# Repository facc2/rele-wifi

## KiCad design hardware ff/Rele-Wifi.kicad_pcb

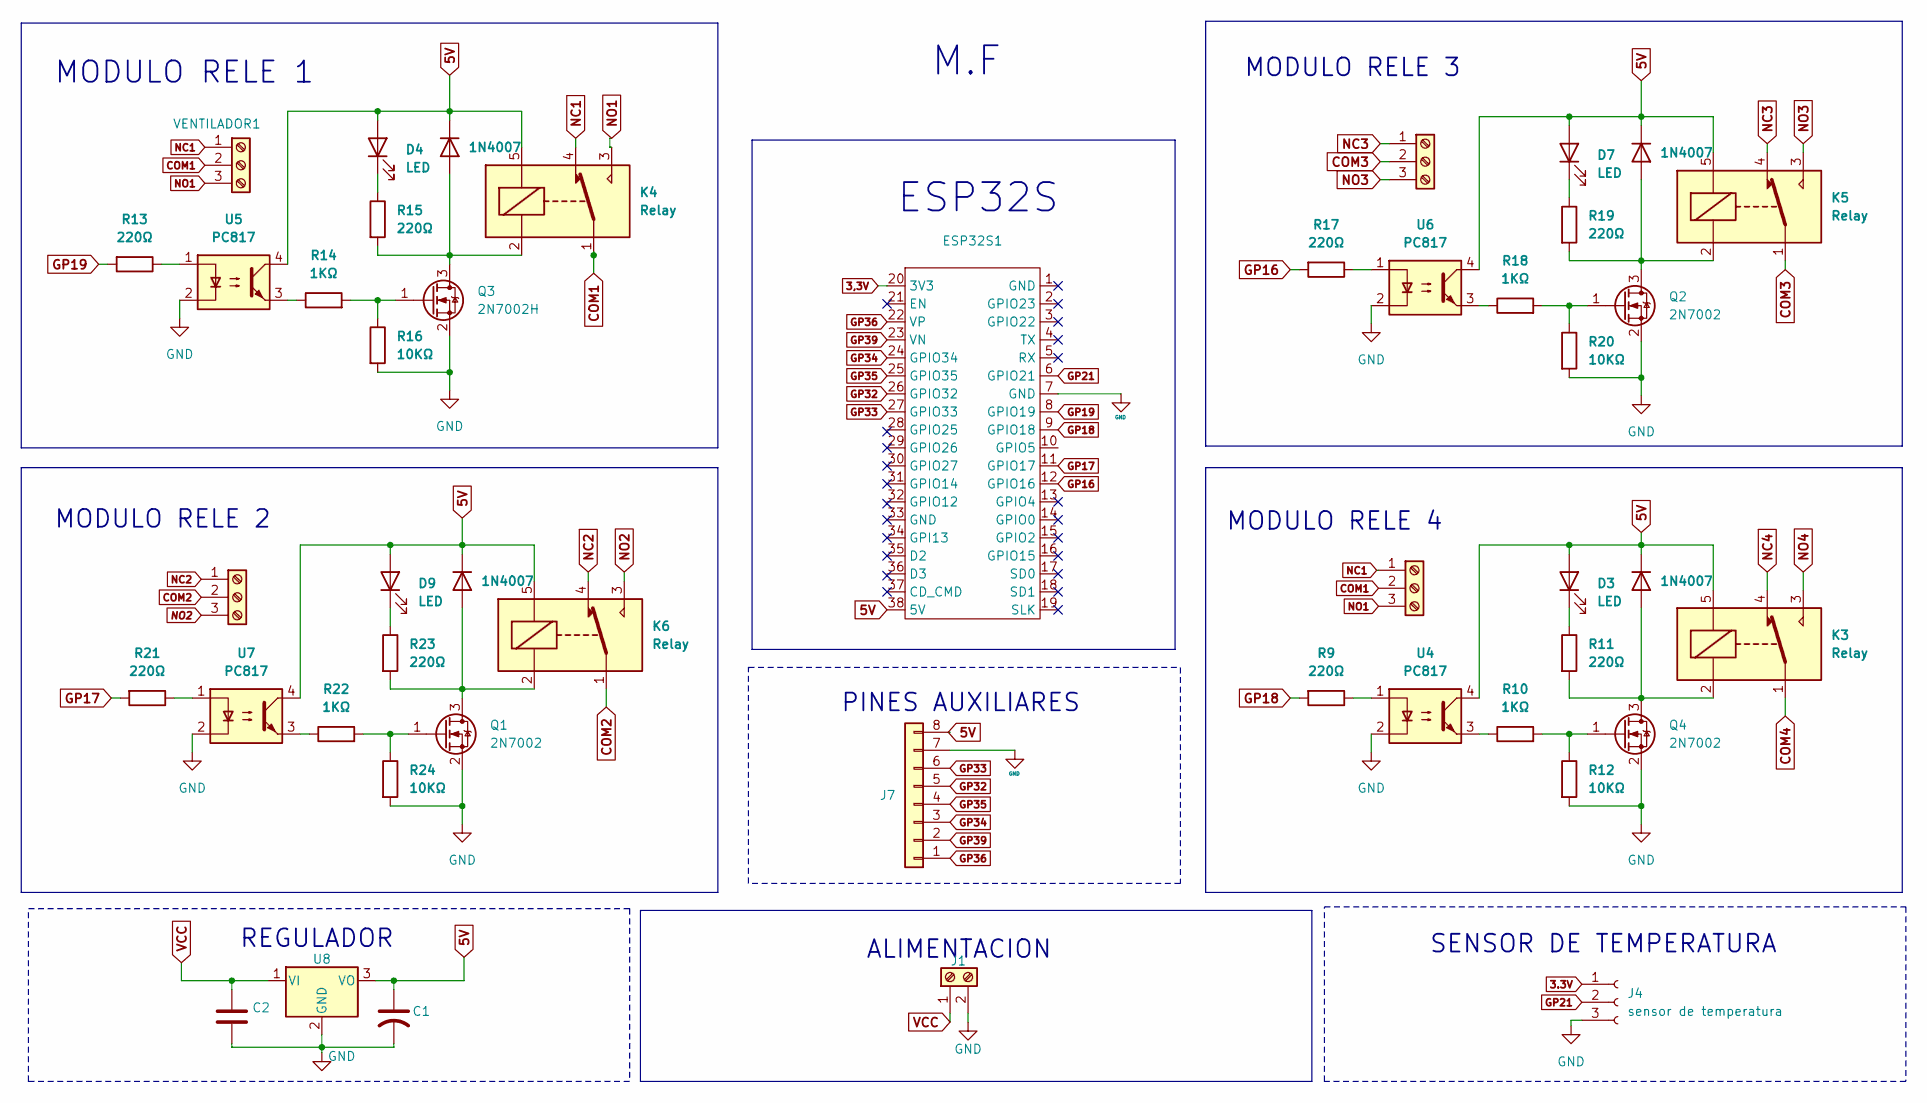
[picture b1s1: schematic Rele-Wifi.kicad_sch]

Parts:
C1: C_US; C_0805_2012Metric
C2: C; C_0805_2012Metric
D3, D4, D7, D9: LED; LED_0805_2012Metric
D5, D6, D8, D10: 1N4007; D_SMA
ESP32S1: ESP32S_38_PINES
J1: Screw_Terminal_01x02; TerminalBlock_MaiXu_MX126-5.0-02P_1x02_P5.00mm
J3, J5, J6: Screw_Terminal_01x03; TerminalBlock_MaiXu_MX126-5.0-03P_1x03_P5.00mm
J4: sensor de temperatura; PinSocket_1x03_P2.54mm_Vertical
J7: Conn_01x08; PinSocket_1x08_P2.54mm_Vertical
K3, K4, K5, K6: Relay; Relay_SPDT_SANYOU_SRD_Series_Form_C
Q1, Q2, Q4: 2N7002; SOT-23
Q3: 2N7002H; SOT-23
R9, R11, R13, R15, R17, R19, R21, R23: 220Ω; R_0805_2012Metric
R10, R14, R18, R22: 1KΩ; R_0805_2012Metric
R12, R16, R20, R24: 10KΩ; R_0805_2012Metric
U4, U5, U6, U7: PC817; DIP-4_W7.62mm
U8: KA78M05_TO252; TO-263-3_TabPin2
VENTILADOR1: Screw_Terminal_01x03; TerminalBlock_MaiXu_MX126-5.0-03P_1x03_P5.00mm

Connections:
3,3V: ESP32S1.20 (3V3)
3.3V: J4.1
5V: C1.1, D3.2 (A), D4.2 (A), D5.1 (K), D6.1 (K), D7.2 (A), D8.1 (K), D9.2 (A), D10.1 (K), ESP32S1.38 (5V), J7.8, K3.5, K4.5, K5.5, K6.5, U4.4, U5.4, U6.4, U7.4, U8.3 (VO)
COM1: J3.2, K4.1, VENTILADOR1.2
COM2: J6.2, K6.1
COM3: J5.2, K5.1
COM4: K3.1
GND: C1.2, C2.2, ESP32S1.7 (GND), J1.2, J4.3, J7.7, Q1.2 (S), Q2.2 (S), Q3.2 (S), Q4.2 (S), R12.2, R16.2, R20.2, R24.2, U4.2, U5.2, U6.2, U7.2, U8.2 (GND)
GP16: ESP32S1.12 (GPIO16), R17.2
GP17: ESP32S1.11 (GPIO17), R21.2
GP18: ESP32S1.9 (GPIO18), R9.2
GP19: ESP32S1.8 (GPIO19), R13.2
GP21: ESP32S1.6 (GPIO21), J4.2
GP32: ESP32S1.26 (GPIO32), J7.5
GP33: ESP32S1.27 (GPIO33), J7.6
GP34: ESP32S1.24 (GPIO34), J7.3
GP35: ESP32S1.25 (GPIO35), J7.4
GP36: ESP32S1.22 (VP), J7.1
GP39: ESP32S1.23 (VN), J7.2
NC1: J3.1, K4.4, VENTILADOR1.1
NC2: J6.1, K6.4
NC3: J5.1, K5.4
NC4: K3.4
NO1: J3.3, K4.3, VENTILADOR1.3
NO2: J6.3, K6.3
NO3: J5.3, K5.3
NO4: K3.3
unnamed: D3.1 (K), R11.1
unnamed: D4.1 (K), R15.1
unnamed: D5.2 (A), K3.2, Q4.3 (D), R11.2
unnamed: D6.2 (A), K4.2, Q3.3 (D), R15.2
unnamed: D7.1 (K), R19.1
unnamed: D8.2 (A), K5.2, Q2.3 (D), R19.2
unnamed: D9.1 (K), R23.1
unnamed: D10.2 (A), K6.2, Q1.3 (D), R23.2
unnamed: Q1.1 (G), R22.2, R24.1
unnamed: Q2.1 (G), R18.2, R20.1
unnamed: Q3.1 (G), R14.2, R16.1
unnamed: Q4.1 (G), R10.2, R12.1
unnamed: R9.1, U4.1
unnamed: R10.1, U4.3
unnamed: R13.1, U5.1
unnamed: R14.1, U5.3
unnamed: R17.1, U6.1
unnamed: R18.1, U6.3
unnamed: R21.1, U7.1
unnamed: R22.1, U7.3
VCC: C2.1, J1.1, U8.1 (VI)

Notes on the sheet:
MODULO RELE 3
MODULO RELE 4
ESP32S
MODULO RELE 1
M.F
ALIMENTACION
SENSOR DE TEMPERATURA
REGULADOR
PINES AUXILIARES
MODULO RELE 2

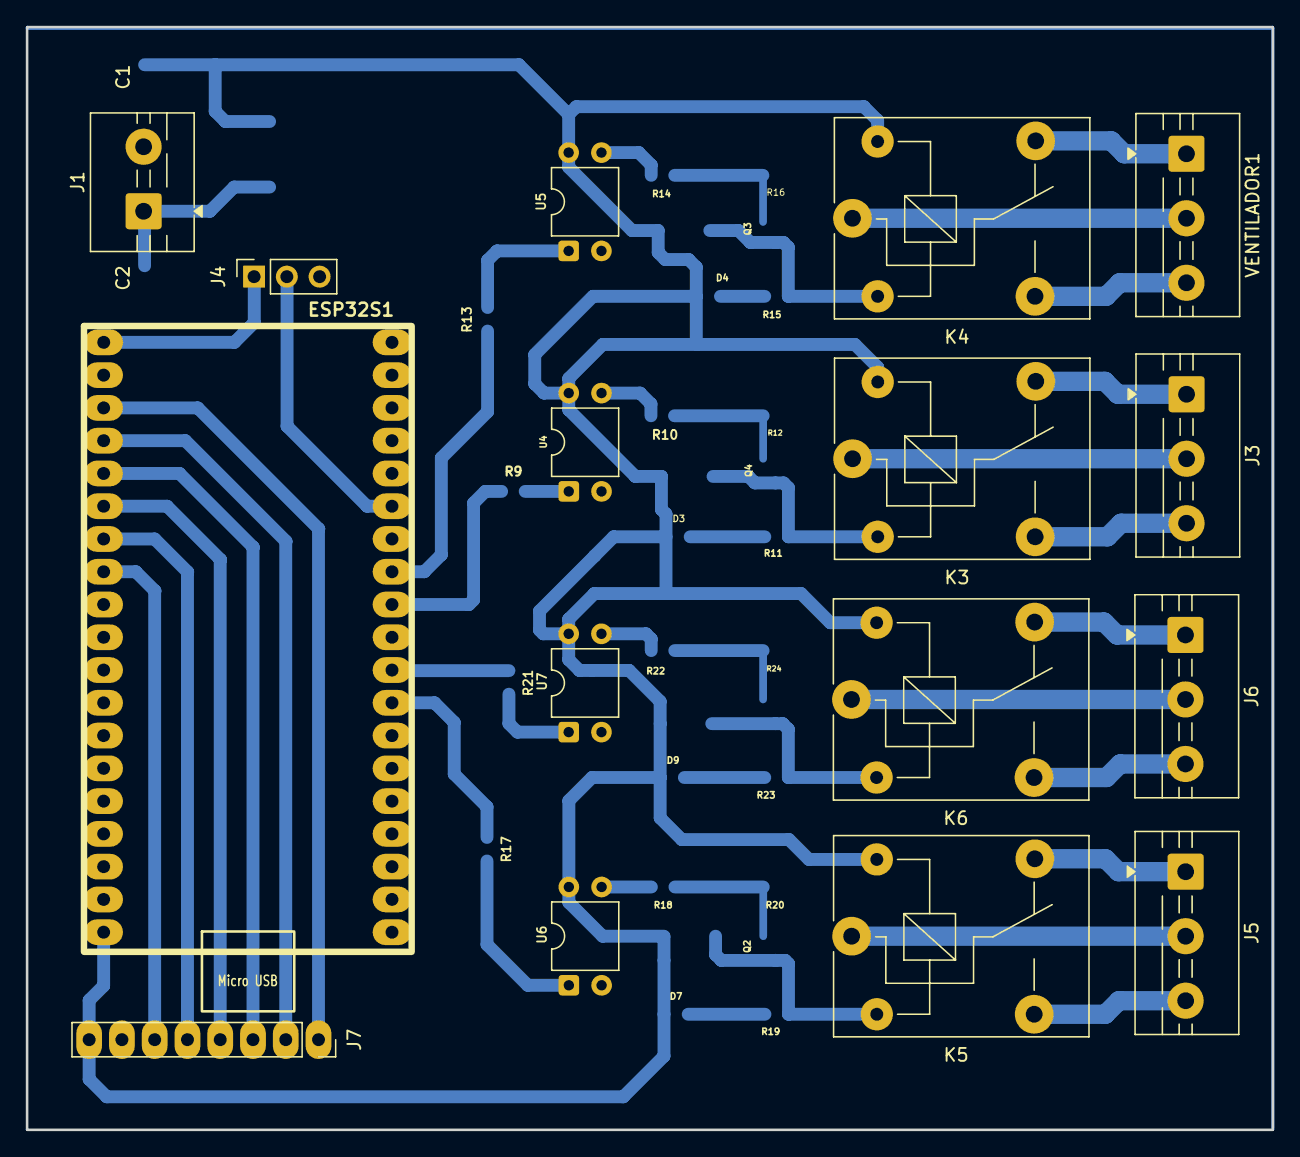
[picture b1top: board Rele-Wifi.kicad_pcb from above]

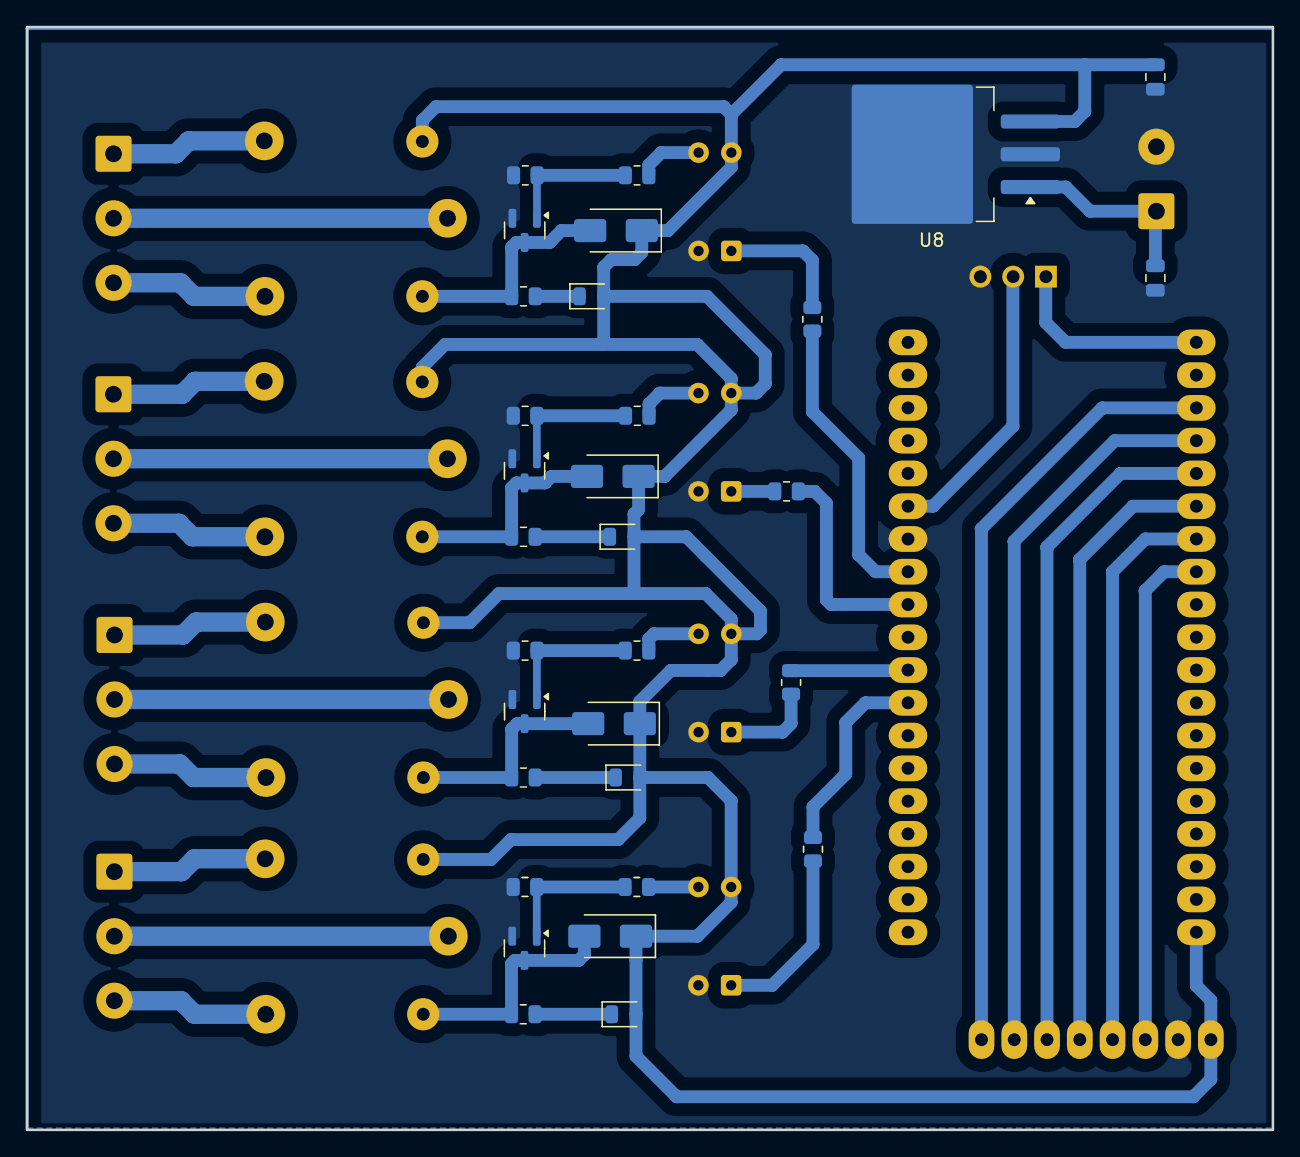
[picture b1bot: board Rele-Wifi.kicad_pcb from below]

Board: 2 copper layers, 96.6 x 85.5 mm, 47 parts (31 on the bottom side), 43 nets.

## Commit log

2025-05-13 Add files via upload
    esquematico
2025-06-25 1.1
    Esquematico
2025-07-02 0.1 code
2025-10-15 Update kkk
2025-12-16 Create DIseño 3D
